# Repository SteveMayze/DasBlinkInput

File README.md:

# DasBlinkInput
Light to digital signal project as part of the Contextual Electonics suite of projects

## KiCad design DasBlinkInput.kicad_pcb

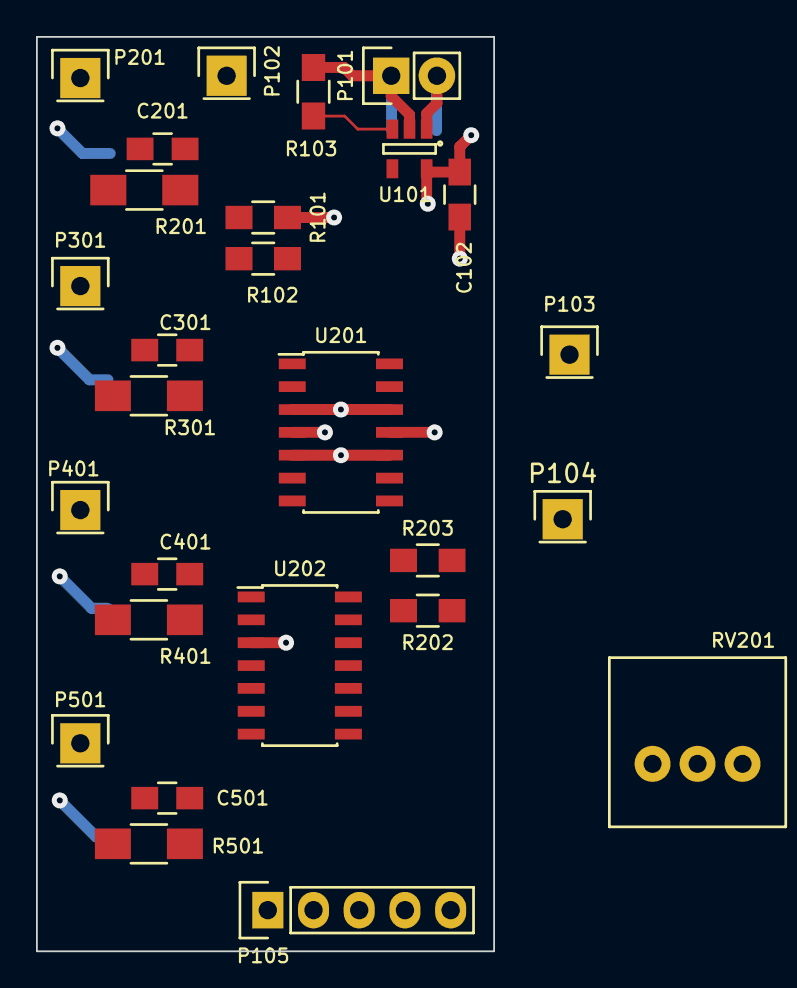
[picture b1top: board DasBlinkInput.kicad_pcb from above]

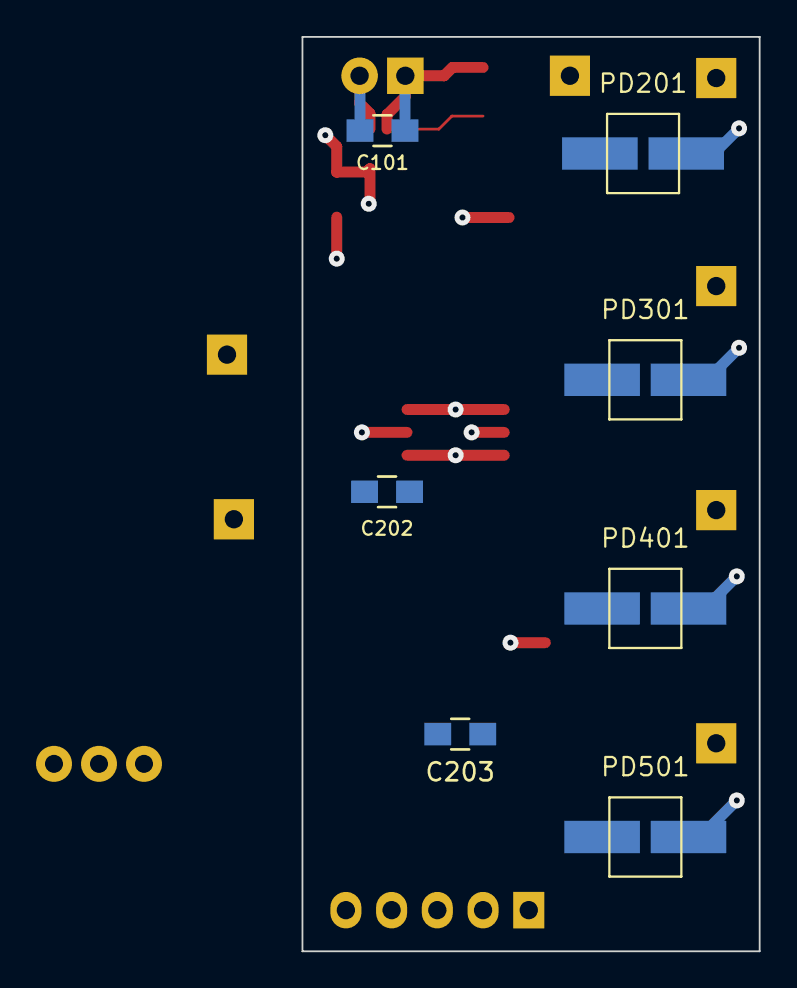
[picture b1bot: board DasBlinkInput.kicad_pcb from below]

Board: 4 copper layers, 25.4 x 50.8 mm, 34 parts (7 on the bottom side), 19 nets.

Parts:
C101, C102: 1U; C_0805_HandSoldering
C201, C301, C401, C501: 100p; C_0805_HandSoldering
C202, C203: 0.1U; C_0805_HandSoldering
P101: Vin; Pin_Header_Straight_1x02
P102: VGND; Pin_Header_Straight_1x01
P103: 3V; Pin_Header_Straight_1x01
P104: GND; Pin_Header_Straight_1x01
P105: Output; Pin_Header_Straight_1x05
P201: Sig1; Pin_Header_Straight_1x01
P301: Sig2; Pin_Header_Straight_1x01
P401: Sig3; Pin_Header_Straight_1x01
P501: Sig4; Pin_Header_Straight_1x01
PD201, PD301, PD401, PD501: VBPW34SR; VBPW34SR*
R101, R102, R202, R203: 10K; R_0805_HandSoldering
R103: 0; R_0805_HandSoldering
R201, R301, R401, R501: 1MEG; R_1206_HandSoldering
RV201: POT; P090L-02F25BR10K
U101: LP2980IM5-3.0/NOPB; SOT-23-5
U201: MCP6404; SOIC-14_3.9x8.7mm_Pitch1.27mm
U202: LM339; SOIC-14_3.9x8.7mm_Pitch1.27mm

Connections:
3V: C102.1, C202.2, C203.2, P103.1, R101.1, R203.2, U101.5, U201.4, U202.3
/Channel 1 Photodetect/Channel1_Out: P105.1, U202.2
/Channel 2 Photodetect/Channel2_Out: P105.2, U202.1
/Channel 2 Photodetect/REF_IN: R202.2, RV201.3, U202.4, U202.6, U202.8, U202.10
/Channel 3 PhotoDetect/Channel3_Out: P105.3, U202.13
/Channel 4 PhotoDetect/Channel4_Out: P105.4, U202.14
GND: C101.2, C102.2, C202.1, C203.1, P101.1, P104.1, P105.5, R102.2, R103.2, R202.1, U101.2, U201.11, U202.12
unnamed: C101.1, P101.2, U101.1
unnamed: C201.1, P201.1, R201.1, U201.1, U202.5
unnamed: C201.2, PD201.2, R201.2, U201.2
unnamed: C301.1, P301.1, R301.1, U201.7, U202.7
unnamed: C301.2, PD301.2, R301.2, U201.6
unnamed: C401.1, P401.1, R401.1, U201.8, U202.11
unnamed: C401.2, PD401.2, R401.2, U201.9
unnamed: C501.1, P501.1, R501.1, U201.14, U202.9
unnamed: C501.2, PD501.2, R501.2, U201.13
unnamed: R103.1, U101.3
unnamed: R203.1, RV201.2
VGND: P102.1, PD201.1, PD301.1, PD401.1, PD501.1, R101.2, R102.1, U201.3, U201.5, U201.10, U201.12

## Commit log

2015-05-16 Initial checkin, upto video 5
2015-05-16 Spice simulation update
2015-05-24 Intermediate commit as at video 16
2015-05-24 Initial layout before starting the connections
2015-05-25 Start of connecting the layout
2015-05-26 Commencting new layout on corrected iPod defintion
2015-05-27 Completed the board layout
2015-05-27 Added POT PDF
2015-05-27 Added layout image for publishing on the build log
2015-06-01 Finalised the board with some logos and generated teh Gerber files
2015-06-01 Added oshpark images for the layouts
2015-06-02 Updated the schematic for the BOM and generated the BOM
2015-06-04 Changes to the BOM
2015-07-04 Added a BOM file
2015-08-29 Checkin before moving to Vagrant
2016-01-08 Clean up and correctsion to the layout. Added the pull up resistors
2020-01-27 Library Corrections
